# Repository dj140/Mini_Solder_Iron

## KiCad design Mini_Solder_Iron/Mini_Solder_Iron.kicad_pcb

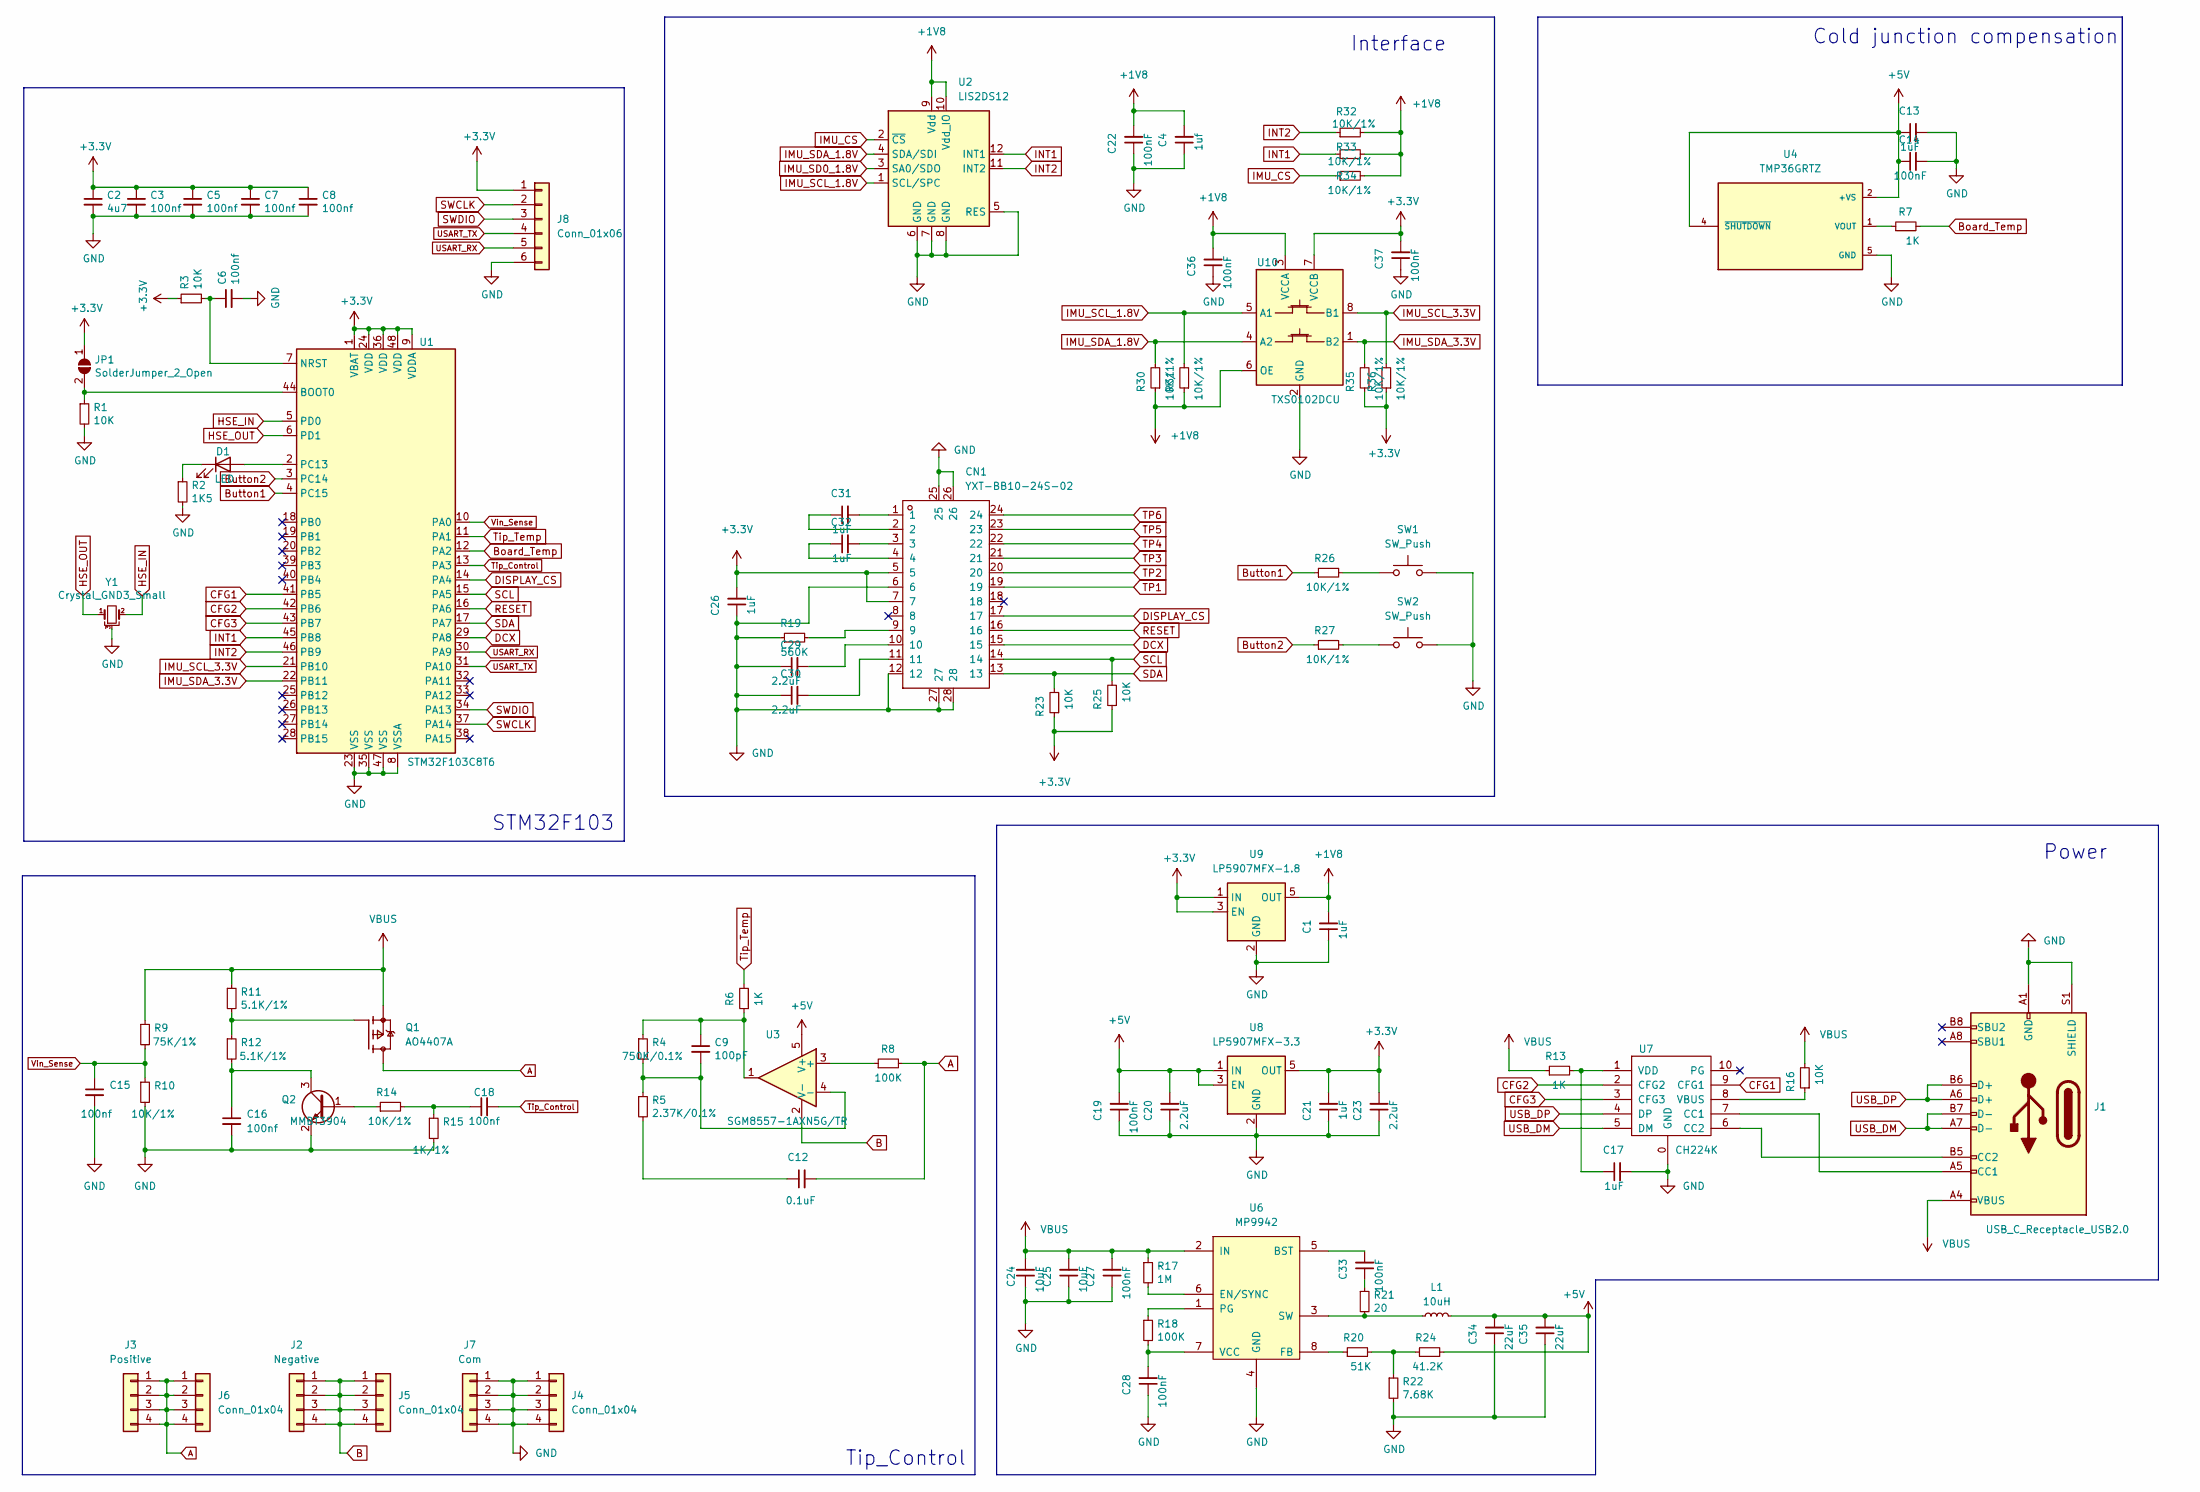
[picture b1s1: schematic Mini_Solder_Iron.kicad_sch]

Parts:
C1, C13, C17, C21, C26, C31, C32: 1uF; C_0402_1005Metric
C2: 4u7; C_0402_1005Metric
C3, C5, C6, C7, C8: 100nf; C_0402_1005Metric
C4: 1uf; C_0402_1005Metric
C9: 100pF; C_0402_1005Metric
C12: 0.1uF; C_0402_1005Metric
C14, C19, C22, C27, C28, C33, C36, C37: 100nF; C_0402_1005Metric
C15, C16, C18: 100nf; C_0402_1005Metric_Pad0.74x0.62mm_HandSolder
C20, C23, C29, C30: 2.2uF; C_0402_1005Metric
C24, C25: 10uF; C_1206_3216Metric
C34, C35: 22uF; C_1206_3216Metric
CN1: YXT-BB10-24S-02; CONN-SMD_YXT-BB10-24S-02
D1: LED; LED_0402_1005Metric
J1: USB_C_Receptacle_USB2.0; USB_C_Receptacle_HRO_TYPE-C-31-M-12
J2: Negative; JBC245_2.4mm
J3: Positive; JBC245_1.5mm
J4: Conn_01x04; JBC245_3.5mm
J5: Conn_01x04; JBC245_2.4mm
J6: Conn_01x04; JBC245_1.5mm
J7: Com; JBC245_3.5mm
J8: Conn_01x06; JST_SH_BM06B-SRSS-TB_1x06-1MP_P1.00mm_Vertical
JP1: SolderJumper_2_Open; SolderJumper-2_P1.3mm_Open_RoundedPad1.0x1.5mm
L1: 10uH; L_Bourns-SRN4018
Q1: AO4407A; SOIC-8-1EP_3.9x4.9mm_P1.27mm_EP2.29x3mm; PARTREV I
Q2: MMBT3904; SOT-23
R1, R3, R16, R23, R25: 10K; R_0402_1005Metric
R2: 1K5; R_0402_1005Metric
R4: 750K/0.1%; R_0402_1005Metric
R5: 2.37K/0.1%; R_0402_1005Metric
R6, R7, R13: 1K; R_0402_1005Metric
R8, R18: 100K; R_0402_1005Metric
R9: 75K/1%; R_0402_1005Metric
R10, R14, R26, R27, R30, R31, R32, R33, R34, R35, R36: 10K/1%; R_0402_1005Metric
R11, R12: 5.1K/1%; R_0402_1005Metric
R15: 1K/1%; R_0402_1005Metric
R17: 1M; R_0402_1005Metric
R19: 560K; R_0402_1005Metric
R20: 51K; R_0402_1005Metric
R21: 20; R_0402_1005Metric
R22: 7.68K; R_0402_1005Metric
R24: 41.2K; R_0402_1005Metric
SW1, SW2: SW_Push; SW_SPST_PTS810
U1: STM32F103C8T6; LQFP-48_7x7mm_P0.5mm
U2: LIS2DS12; LGA-12_2x2mm_P0.5mm
U3: SGM8557-1AXN5G/TR; SOT-23-5
U4: TMP36GRTZ; SOT-23-5; PARTREV H
U6: MP9942; TSOT23-8_L2.9-W1.6-P0.65-LS2.8-BL
U7: CH224K; ESSOP-10_L4.9-W3.9-P1.0-LS6.0-TL-EP
U8: LP5907MFX-3.3; SOT-23-5
U9: LP5907MFX-1.8; SOT-23-5
U10: TXS0102DCU; VSSOP-8_2.3x2mm_P0.5mm
Y1: Crystal_GND3_Small; OSC_CSTCE8M00G55-R0

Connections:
+1V8: C1.2, C4.2, C22.2, C36.2, R30.1, R31.1, R32.2, R33.2, R34.2, U2.9 (Vdd), U2.10 (Vdd_IO), U9.5 (OUT), U10.3 (VCCA), U10.6 (OE)
+3V3: C2.1, C3.1, C5.1, C7.1, C8.1, C21.2, C23.2, C26.2, C37.2, CN1.5, CN1.7, J8.1, JP1.1 (A), R3.1, R23.1, R25.1, R35.1, R36.1, U1.1 (VBAT), U1.9 (VDDA), U1.24 (VDD), U1.36 (VDD), U1.48 (VDD), U8.5 (OUT), U9.1 (IN), U9.3 (EN), U10.7 (VCCB)
+5V: C13.1, C14.1, C19.2, C20.2, C34.2, C35.2, L1.2, R24.2, U3.5 (V+), U4.2 (+VS), U4.4 (~SHUTDOWN), U8.1 (IN), U8.3 (EN)
A: C12.2, J3.1, J3.2, J3.3, J3.4, J6.1, J6.2, J6.3, J6.4, Q1.5, Q1.6, Q1.7, Q1.8, R8.2
B: J2.1, J2.2, J2.3, J2.4, J5.1, J5.2, J5.3, J5.4, U3.2 (V-)
Board_Temp: R7.2, U1.12 (PA2)
Button1: R26.1, U1.4 (PC15)
Button2: R27.1, U1.3 (PC14)
CFG1: U1.41 (PB5), U7.9 (CFG1)
CFG2: U1.42 (PB6), U7.2 (CFG2)
CFG3: U1.43 (PB7), U7.3 (CFG3)
DCX: CN1.15, U1.29 (PA8)
DISPLAY_CS: CN1.17, U1.14 (PA4)
GND: C1.1, C2.2, C3.2, C4.1, C5.2, C6.2, C7.2, C8.2, C13.2, C14.2, C15.2, C16.2, C17.2, C19.1, C20.1, C21.1, C22.1, C23.1, C24.1, C25.1, C26.1, C27.1, C28.1, C29.1, C30.1, C34.1, C35.1, C36.1, C37.1, CN1.6, CN1.12, CN1.25, CN1.26, CN1.27, CN1.28, J1.A1 (GND), J1.A12 (GND), J1.B1 (GND), J1.B12 (GND), J1.S1 (SHIELD), J4.1, J4.2, J4.3, J4.4, J7.1, J7.2, J7.3, J7.4, J8.6, Q2.2 (E), R1.2, R2.2, R10.2, R15.2, R19.1, R22.2, SW1.2, SW2.2, U1.8 (VSSA), U1.23 (VSS), U1.35 (VSS), U1.47 (VSS), U2.5 (RES), U2.6 (GND), U2.7 (GND), U2.8 (GND), U4.5 (GND), U6.4 (GND), U7.0 (GND), U8.2 (GND), U9.2 (GND), U10.2 (GND), Y1.3
HSE_IN: U1.5 (PD0), Y1.2
HSE_OUT: U1.6 (PD1), Y1.1
IMU_CS: R34.1, U2.2 (~CS)
IMU_SCL_1.8V: R31.2, U2.1 (SCL/SPC), U10.5 (A1)
IMU_SCL_3.3V: R36.2, U1.21 (PB10), U10.8 (B1)
IMU_SD0_1.8V: U2.3 (SA0/SDO)
IMU_SDA_1.8V: R30.2, U2.4 (SDA/SDI), U10.4 (A2)
IMU_SDA_3.3V: R35.2, U1.22 (PB11), U10.1 (B2)
INT1: R33.1, U1.45 (PB8), U2.12 (INT1)
INT2: R32.1, U1.46 (PB9), U2.11 (INT2)
unnamed: C6.1, R3.2, U1.7 (NRST)
unnamed: C9.1, R4.1, R6.1, U3.1
unnamed: C9.2, R4.2, R5.1, U3.4 (-)
unnamed: C12.1, R5.2
unnamed: C16.1, Q2.3 (C), R12.2
unnamed: C17.1, R13.2, U7.1 (VDD)
unnamed: C18.1, R14.2, R15.1
unnamed: C28.2, R18.2, U6.7 (VCC)
unnamed: C29.2, CN1.10
unnamed: C30.2, CN1.11
unnamed: C31.1, CN1.2
unnamed: C31.2, CN1.1
unnamed: C32.1, CN1.4
unnamed: C32.2, CN1.3
unnamed: C33.1, R21.1
unnamed: C33.2, U6.5 (BST)
unnamed: CN1.9, R19.2
unnamed: D1.1 (K), R2.1
unnamed: D1.2 (A), U1.2 (PC13)
unnamed: J1.A5 (CC1), U7.7 (CC1)
unnamed: J1.B5 (CC2), U7.6 (CC2)
unnamed: JP1.2 (B), R1.1, U1.44 (BOOT0)
unnamed: L1.1, R21.2, U6.3 (SW)
unnamed: Q1.4, R11.2, R12.1
unnamed: Q2.1 (B), R14.1
unnamed: R7.1, U4.1 (VOUT)
unnamed: R8.1, U3.3 (+)
unnamed: R16.1, U7.8 (VBUS)
unnamed: R17.2, U6.6 (EN/SYNC)
unnamed: R18.1, U6.1 (PG)
unnamed: R20.1, U6.8 (FB)
unnamed: R20.2, R22.1, R24.1
unnamed: R26.2, SW1.1
unnamed: R27.2, SW2.1
RESET: CN1.16, U1.16 (PA6)
SCL: CN1.14, R25.2, U1.15 (PA5)
SDA: CN1.13, R23.2, U1.17 (PA7)
SWCLK: J8.2, U1.37 (PA14)
SWDIO: J8.3, U1.34 (PA13)
TP1: CN1.19
TP2: CN1.20
TP3: CN1.21
TP4: CN1.22
TP5: CN1.23
TP6: CN1.24
Tip_Control: C18.2, U1.13 (PA3)
Tip_Temp: R6.2, U1.11 (PA1)
USART_RX: J8.5, U1.30 (PA9)
USART_TX: J8.4, U1.31 (PA10)
USB_DM: J1.A7 (D-), J1.B7 (D-), U7.5 (DM)
USB_DP: J1.A6 (D+), J1.B6 (D+), U7.4 (DP)
VBUS: C24.2, C25.2, C27.2, J1.A4 (VBUS), J1.A9 (VBUS), J1.B4 (VBUS), J1.B9 (VBUS), Q1.1, Q1.2, Q1.3, R9.1, R11.1, R13.1, R16.2, R17.1, U6.2 (IN)
Vin_Sense: C15.1, R9.2, R10.1, U1.10 (PA0)

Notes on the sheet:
Power
Tip_Control
STM32F103
Cold junction compensation
Interface

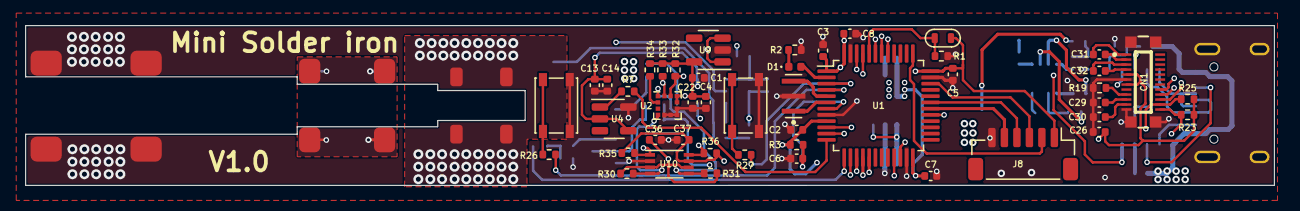
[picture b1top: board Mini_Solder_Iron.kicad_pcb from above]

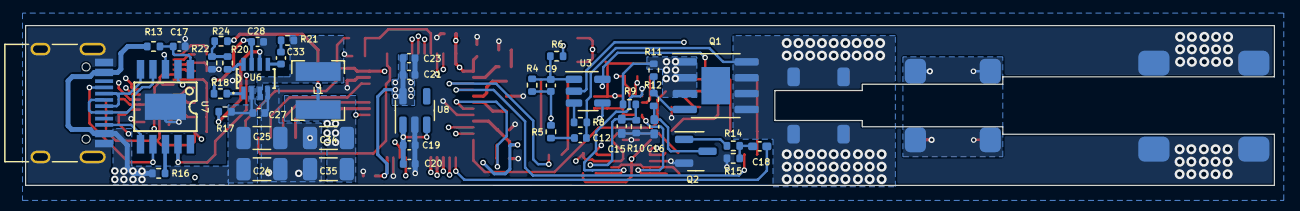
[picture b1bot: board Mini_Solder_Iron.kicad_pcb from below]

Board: 4 copper layers, 100.0 x 12.8 mm, 95 parts (46 on the bottom side), 70 nets.

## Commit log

2022-10-12 PCB layout update
